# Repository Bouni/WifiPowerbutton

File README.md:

# WifiPowerButton

This small PCB let me control my home server remotly over WiFi.

My home server in my basement consists of a Asrock J3455-ITX which runs all my stuff and consumes relatively little power.
Unfortunately it dies every 2 months or so which requires me to go to the basement and reboot it.
That happen normally at the most inconvinient times and I hope that this little board lets me rebot it from everywhere in the world given my Internet connection works.
The brains of this project will be a WEMOS S2 mini because I have a dozen or so laying around ...

## Pictures

## Pinout

## Firmware

ToDo ...

I plan to use ESPHome for that.

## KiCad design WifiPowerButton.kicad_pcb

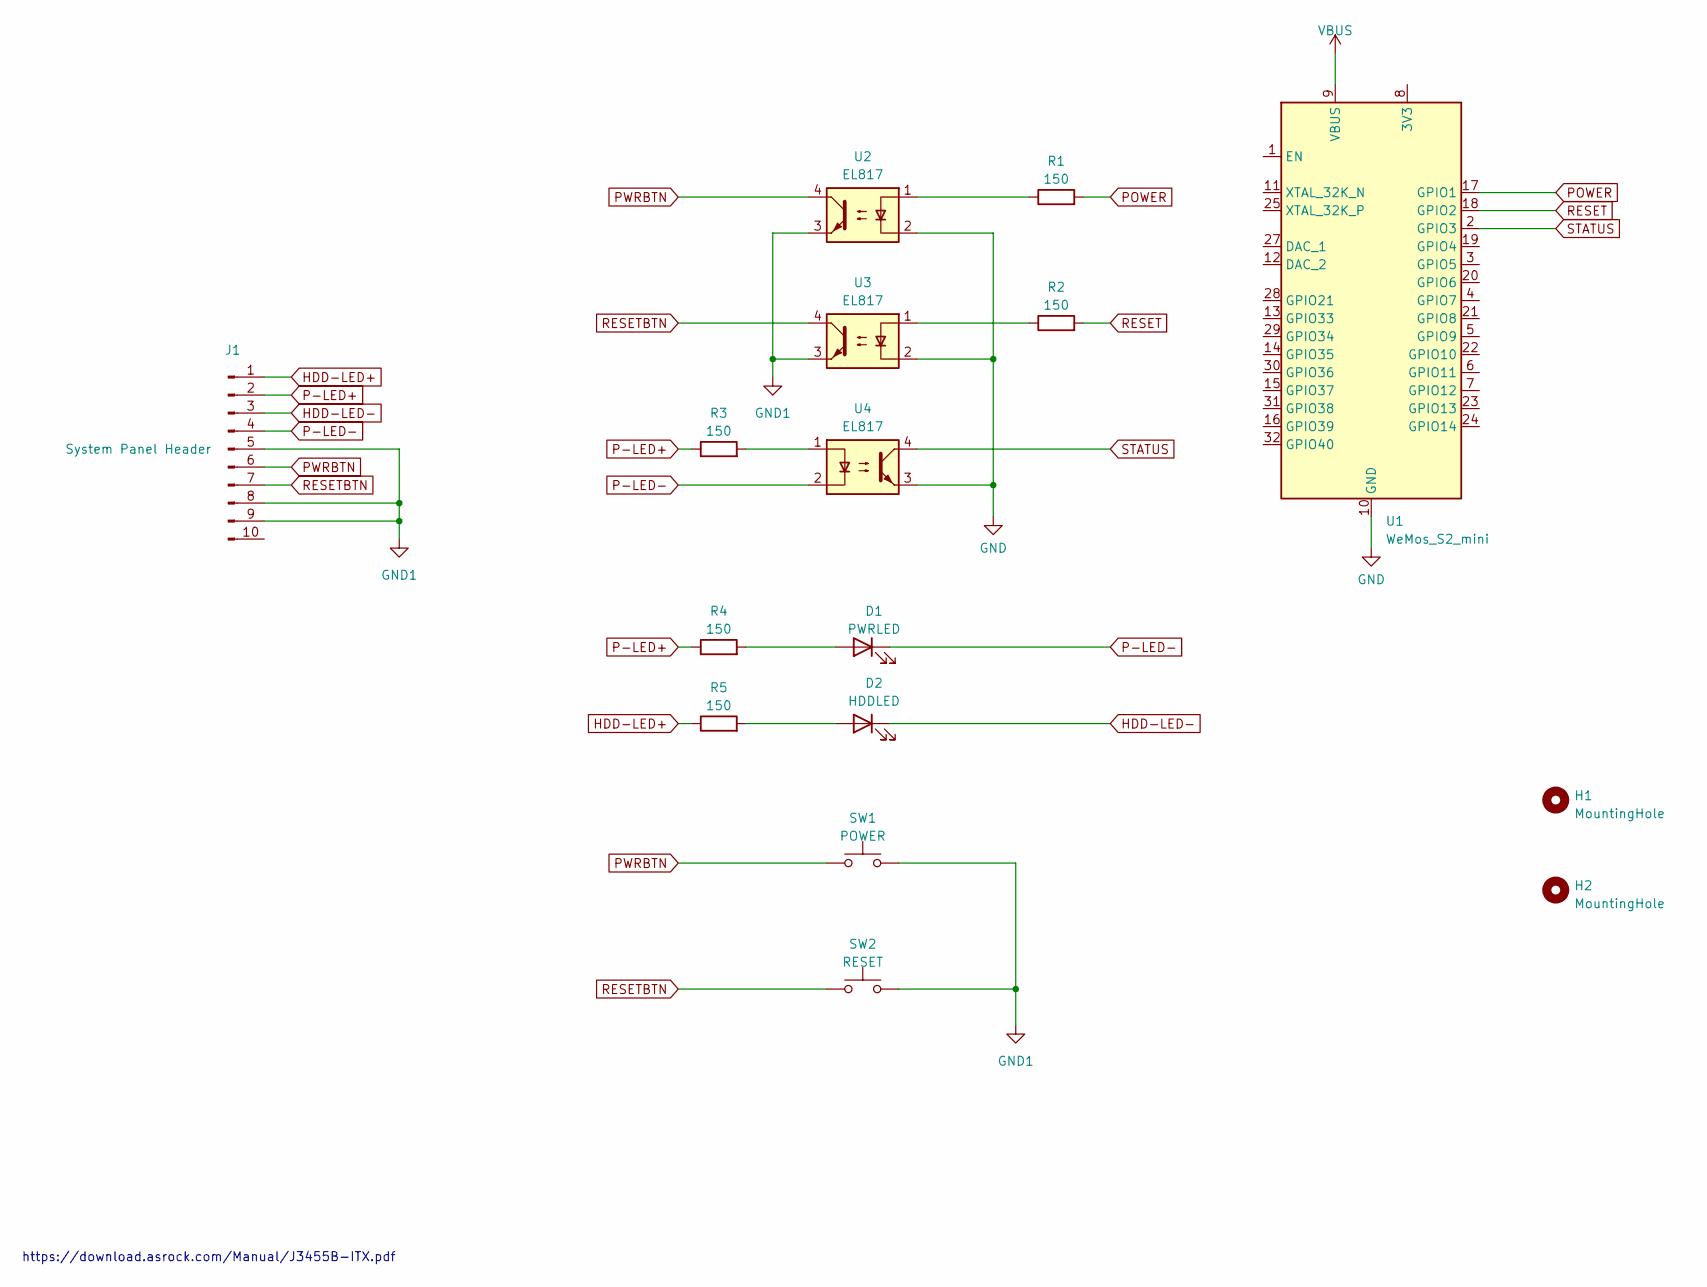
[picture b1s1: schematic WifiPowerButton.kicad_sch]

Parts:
D1: PWRLED; LED_0603_1608Metric
D2: HDDLED; LED_0603_1608Metric
H1, H2: MountingHole; MountingHole_3.2mm_M3
J1: System Panel Header; PinHeader_2x05_P2.54mm_Vertical
R1, R2, R3, R4, R5: 150; R_0603_1608Metric
SW1: POWER; SW_PUSH_6mm_H5mm
SW2: RESET; SW_PUSH_6mm_H5mm
U1: WeMos_S2_mini; WEMOS_S2_mini
U2, U3, U4: EL817; DIP-4_W7.62mm_SMDSocket_SmallPads

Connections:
GND: U1.10 (GND), U1.26 (GND), U2.2, U3.2, U4.3
GND1: J1.5, J1.8, J1.9, SW1.2, SW2.2, U2.3, U3.3
HDD-LED+: J1.1, R5.1
HDD-LED-: D2.1 (K), J1.3
unnamed: D1.2 (A), R4.2
unnamed: D2.2 (A), R5.2
unnamed: R1.1, U2.1
unnamed: R2.1, U3.1
unnamed: R3.2, U4.1
P-LED+: J1.2, R3.1, R4.1
P-LED-: D1.1 (K), J1.4, U4.2
POWER: R1.2, U1.17 (GPIO1)
PWRBTN: J1.6, SW1.1, U2.4
RESET: R2.2, U1.18 (GPIO2)
RESETBTN: J1.7, SW2.1, U3.4
STATUS: U1.2 (GPIO3), U4.4
VBUS: U1.9 (VBUS)

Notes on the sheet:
https://download.asrock.com/Manual/J3455B-ITX.pdf

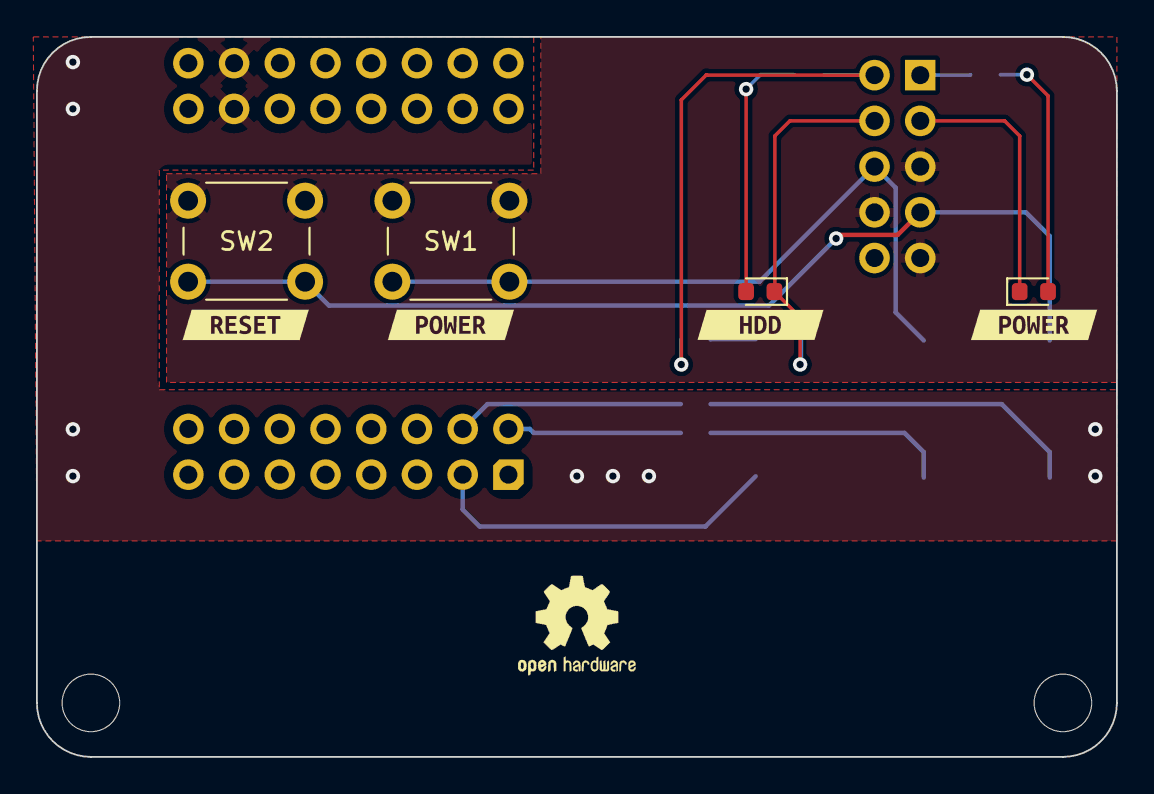
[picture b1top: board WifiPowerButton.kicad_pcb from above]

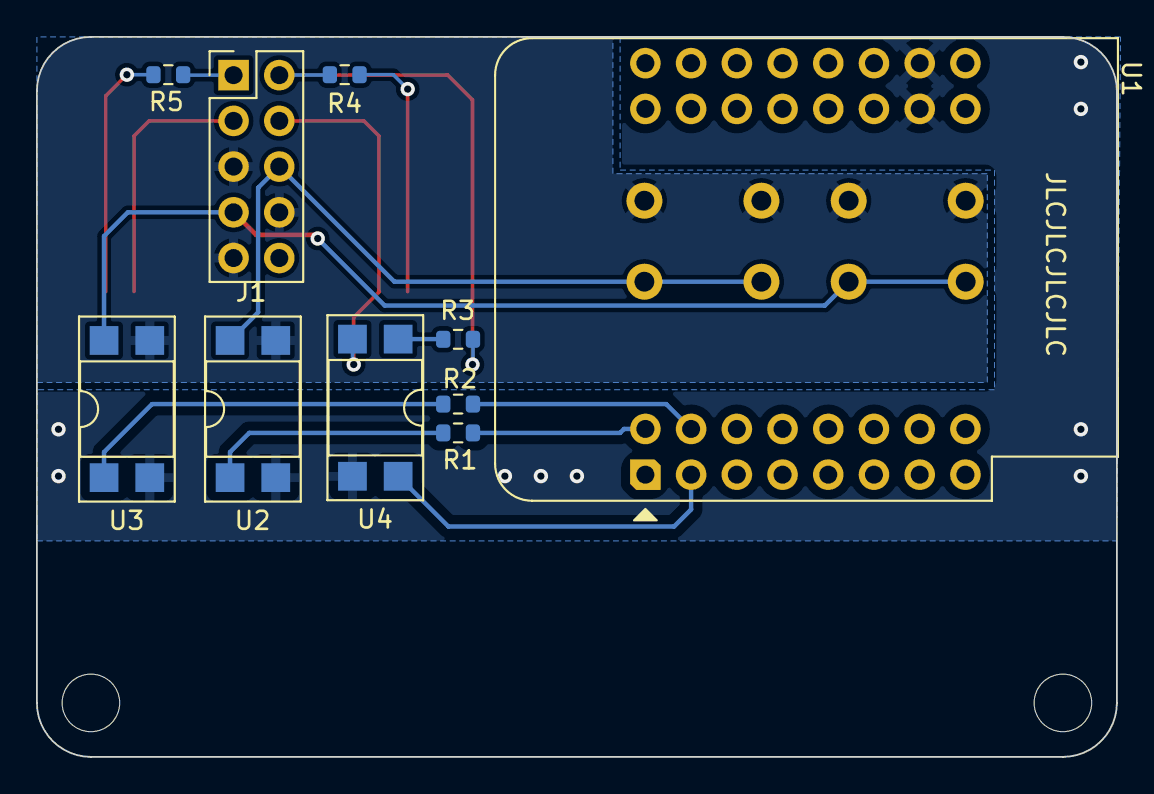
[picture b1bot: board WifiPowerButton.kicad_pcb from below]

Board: 2 copper layers, 60.0 x 40.0 mm, 20 parts (10 on the bottom side), 16 nets.

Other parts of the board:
kibuzzard-6435667C: G***; kibuzzard-6435667C
kibuzzard-6435675A: G***; kibuzzard-6435675A
kibuzzard-64356661: G***; kibuzzard-64356661
kibuzzard-64356751: G***; kibuzzard-64356751

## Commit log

2023-04-13 Add pictures and README
2023-04-13 Add Licence
